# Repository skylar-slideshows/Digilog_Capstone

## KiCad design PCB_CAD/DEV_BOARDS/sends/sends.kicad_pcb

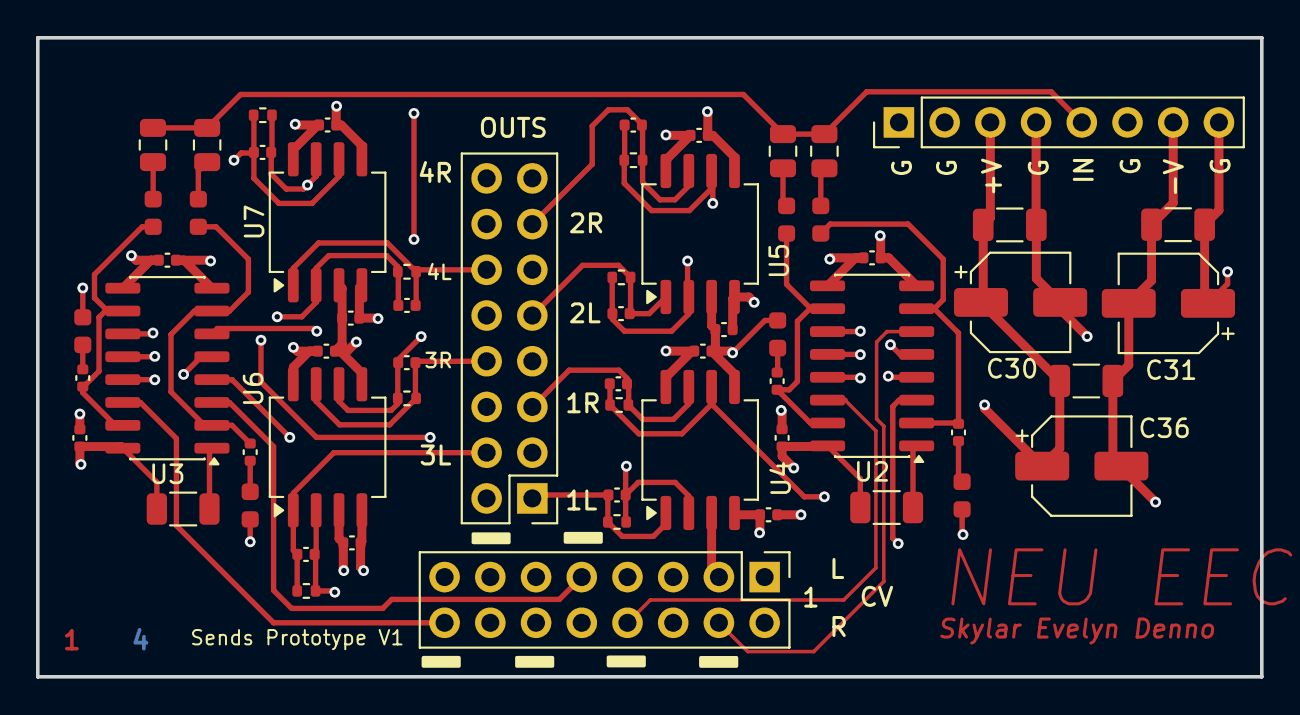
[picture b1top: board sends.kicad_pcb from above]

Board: 4 copper layers, 68.0 x 35.5 mm, 61 parts (0 on the bottom side), 42 nets.

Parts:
C1, C2, C3, C4, C5, C6, C7, C8: 100p; C_0402_1005Metric
C9, C11, C13, C14: 2.2u; C_0805_2012Metric
C10, C12, C15, C16: 1.2n; C_0402_1005Metric
C18, C19, C20, C21, C22, C23, C24, C25, C26, C27, C28, C29: 100n; C_0402_1005Metric
C30, C31, C36: 10u; CP_Elec_5x5.8
C34, C35, C37: 1u; C_1206_3216Metric
J1, J2: Conn_02x08_Odd_Even; PinHeader_2x08_P2.54mm_Vertical
J3: Conn_01x08_Pin; PinHeader_1x08_P2.54mm_Vertical
R1, R2, R3, R4, R5, R6, R7, R8: 20k; R_0402_1005Metric
R9, R11, R13, R14: 10k; R_0603_1608Metric
R10, R12, R15, R16: 220; R_0603_1608Metric
R17, R18: 15k; R_1206_3216Metric
U2, U3: SSI2164; SOIC-16_3.9x9.9mm_P1.27mm
U4, U5, U6, U7: NE5532; SOIC-8_5.3x6.2mm_P1.27mm

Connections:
1_1L: C1.2, J2.1, R1.2, U4.1
1_1R: C2.2, J2.5, R2.2, U4.7
1_2L: C3.2, J2.9, R3.2, U5.1
1_2R: C4.2, J2.13, R4.2, U5.7
1_3L: C5.2, J2.4, R5.2, U6.1
1_3R: C6.2, J2.8, R6.2, U6.7
1_4L: C7.2, J2.12, R7.2, U7.1
1_4R: C8.2, J2.16, R8.2, U7.7
1_IN: C9.1, C11.1, C13.1, C14.1, J3.5
1_send1L: J1.1, U2.3 (VC1)
1_send1R: J1.4, U2.6 (VC2)
1_send2L: J1.5, U2.11 (VC3)
1_send2R: J1.8, U2.14 (VC4)
1_send3L: J1.9, U3.3 (VC1)
1_send3R: J1.12, U3.6 (VC2)
1_send4L: J1.13, U3.11 (VC3)
1_send4R: J1.16, U3.14 (VC4)
+16.6V: C18.1, C20.1, C22.1, C24.1, C26.1, C28.1, C30.1, C34.1, C36.1, C37.1, J3.3, R17.1, R18.1, U2.16 (V+), U3.16 (V+), U4.8 (V+), U5.8 (V+), U6.8 (V+), U7.8 (V+)
-16.6V: C19.1, C21.1, C23.1, C25.1, C27.1, C29.1, C31.2, C35.1, C36.2, C37.2, J3.7, U2.9 (V-), U3.9 (V-), U4.4 (V-), U5.4 (V-), U6.4 (V-), U7.4 (V-)
GND: C18.2, C19.2, C20.2, C21.2, C22.2, C23.2, C24.2, C25.2, C26.2, C27.2, C28.2, C29.2, C30.2, C31.1, C34.2, C35.2, J1.2, J1.3, J1.6, J1.7, J1.10, J1.11, J1.14, J1.15, J2.2, J2.3, J2.6, J2.7, J2.10, J2.11, J2.14, J2.15, J3.1, J3.2, J3.4, J3.6, J3.8, R10.2, R12.2, R15.2, R16.2, U2.8 (GND), U3.8 (GND), U4.3 (+), U4.5 (+), U5.3 (+), U5.5 (+), U6.3 (+), U6.5 (+), U7.3 (+), U7.5 (+)
unnamed: C9.2, R9.1
unnamed: C10.2, R10.1
unnamed: C11.2, R11.1
unnamed: C12.2, R12.1
unnamed: C13.2, R13.1
unnamed: C14.2, R14.1
unnamed: C15.2, R15.1
unnamed: C16.2, R16.1
unnamed: C10.1, R9.2, U2.2 (I_IN1), U2.7 (I_IN2)
unnamed: C12.1, R11.2, U2.10 (I_IN3), U2.15 (I_IN4)
unnamed: C1.1, R1.1, U2.4 (I_OUT1), U4.2 (-)
unnamed: C2.1, R2.1, U2.5 (I_OUT2), U4.6 (-)
unnamed: C3.1, R3.1, U2.12 (I_OUT3), U5.2 (-)
unnamed: C4.1, R4.1, U2.13 (I_OUT4), U5.6 (-)
unnamed: R17.2, U2.1 (MODE)
unnamed: C15.1, R13.2, U3.2 (I_IN1), U3.7 (I_IN2)
unnamed: C16.1, R14.2, U3.10 (I_IN3), U3.15 (I_IN4)
unnamed: C5.1, R5.1, U3.4 (I_OUT1), U6.2 (-)
unnamed: C6.1, R6.1, U3.5 (I_OUT2), U6.6 (-)
unnamed: C7.1, R7.1, U3.12 (I_OUT3), U7.2 (-)
unnamed: C8.1, R8.1, U3.13 (I_OUT4), U7.6 (-)
unnamed: R18.2, U3.1 (MODE)

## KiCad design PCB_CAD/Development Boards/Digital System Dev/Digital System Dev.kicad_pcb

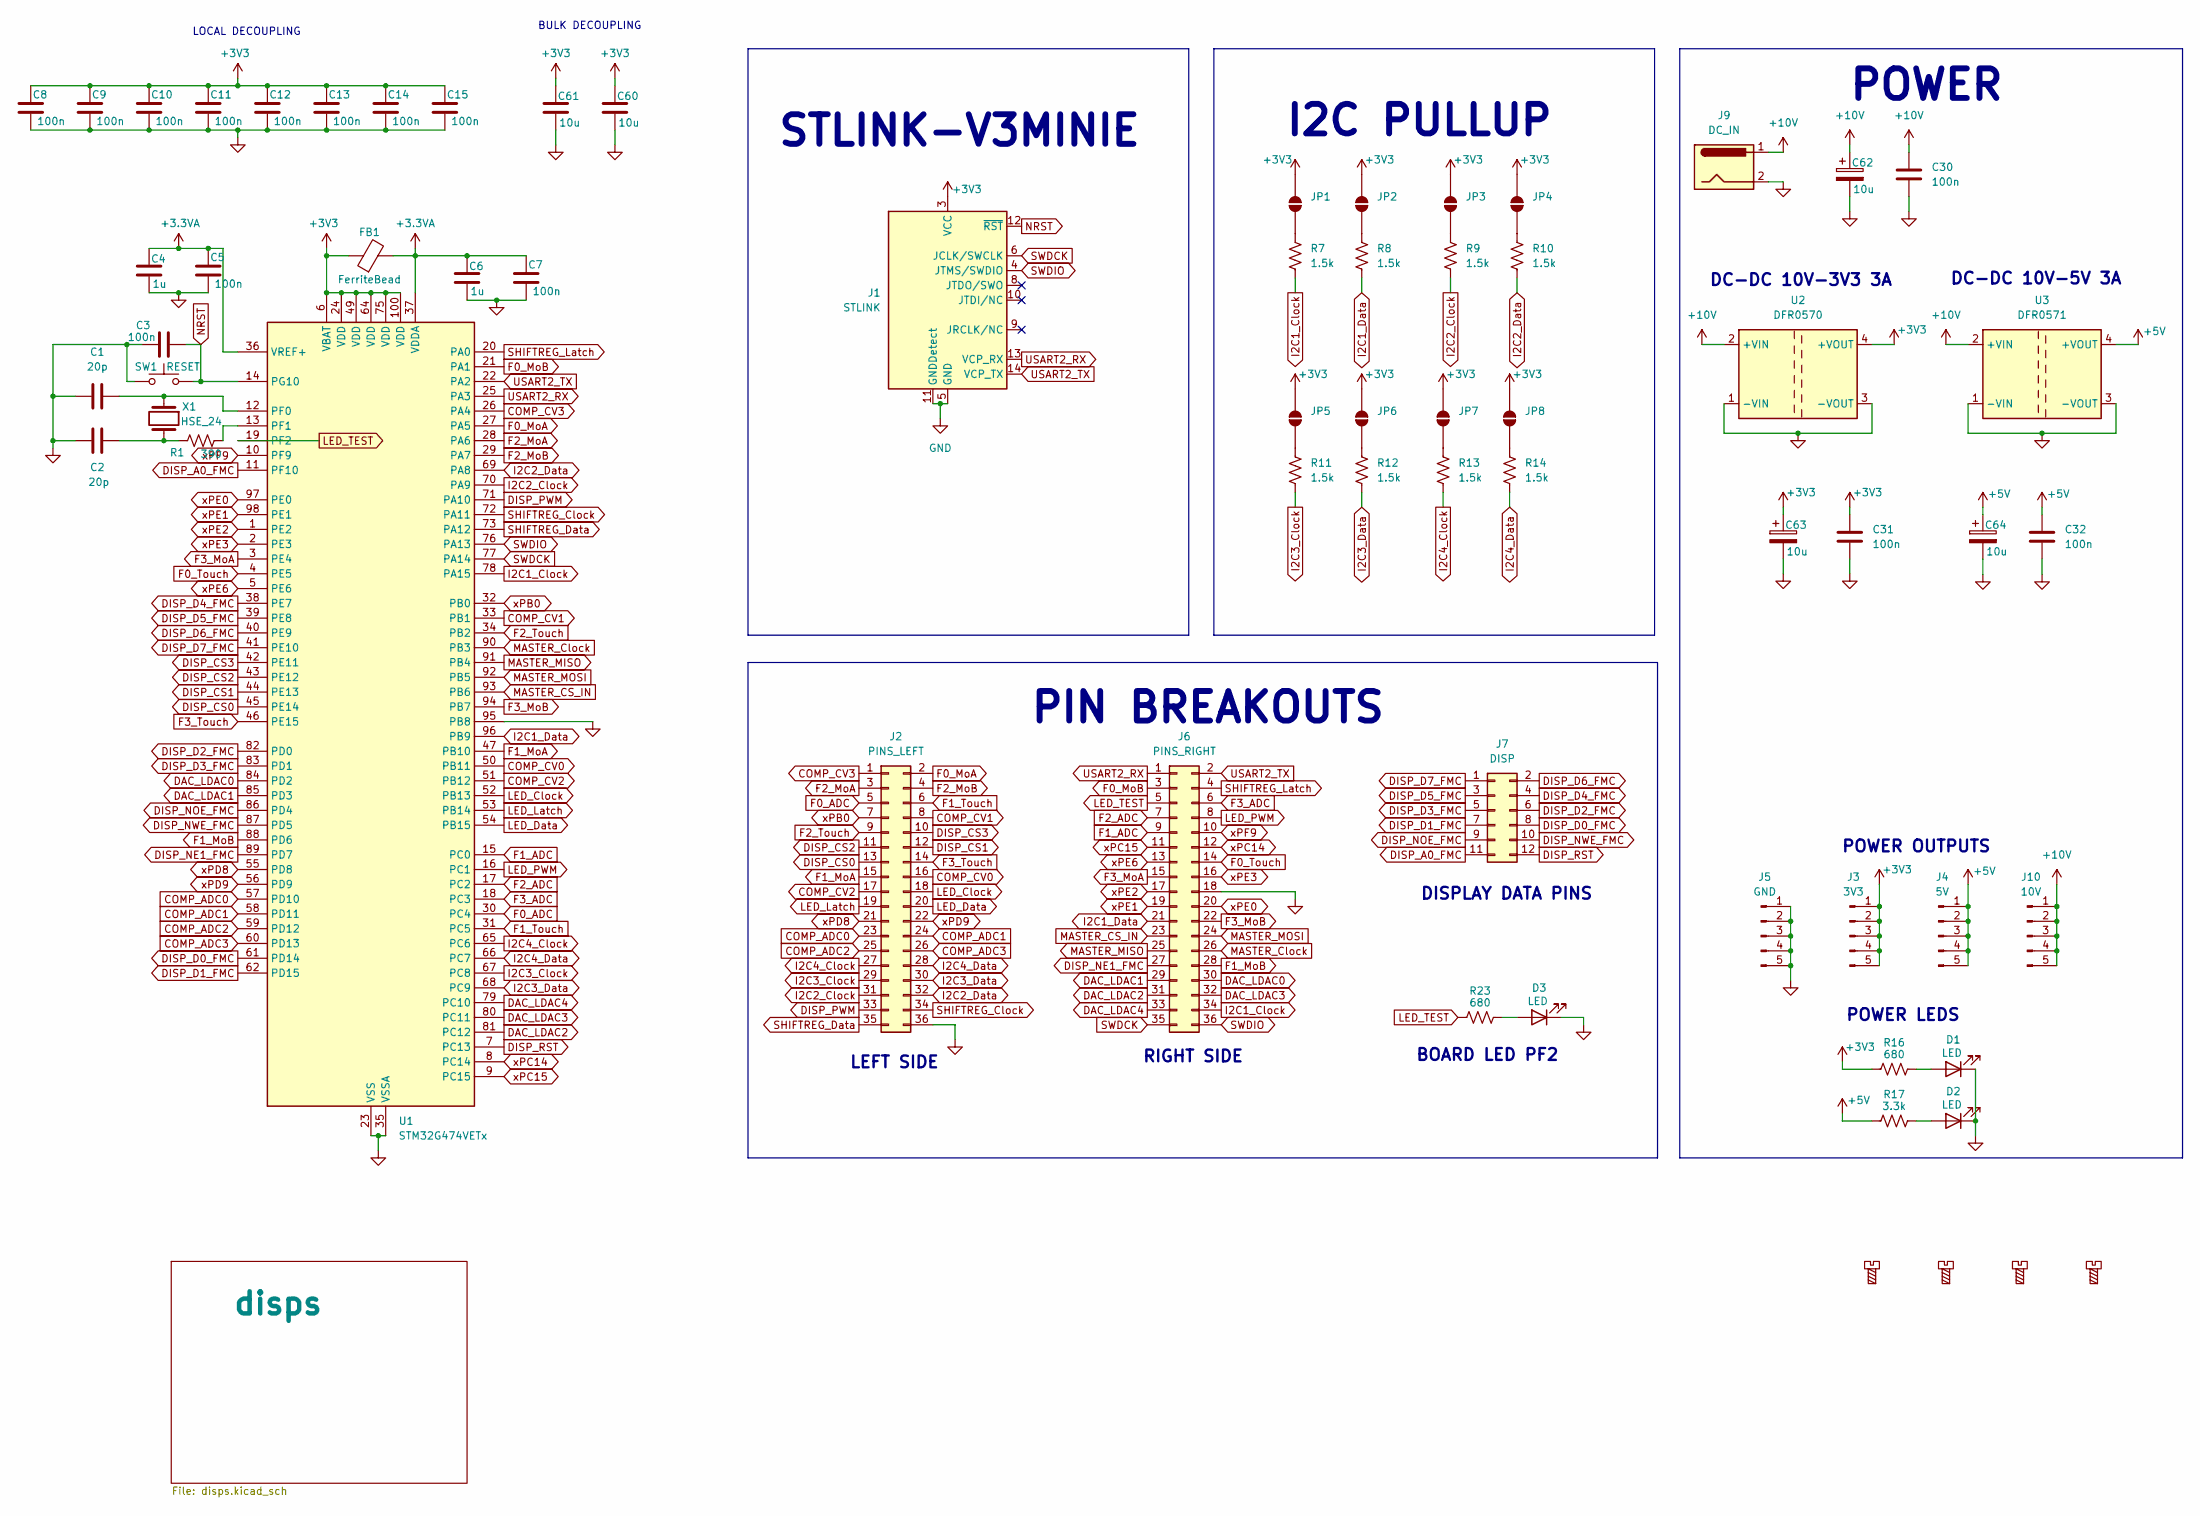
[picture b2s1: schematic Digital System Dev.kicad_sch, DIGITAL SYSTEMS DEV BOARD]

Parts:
C1, C2: 20p; C_0603_1608Metric; LCSC C1648
C3, C5, C7, C8, C9, C10, C11, C12, C13, C14, C15, C30, C31, C32: 100n; C_0603_1608Metric; LCSC C1590
C4, C6: 1u; C_0603_1608Metric; LCSC C1592
C60, C61: 10u; C_1206_3216Metric; LCSC C1849
C62, C63, C64: 10u; CP_Elec_6.3x5.8; LCSC C48970664
D1, D2, D3: LED; LED_0603_1608Metric; LCSC C12065
FB1: FerriteBead; Ferrite_0603_1608Metric; LCSC C1002
H1, H2, H3, H4: MountingScrew; MountingHole_3.2mm_M3; LCSC DNP
J1: STLINK; FTSH-107-01-L-DV-K-TR; LCSC C5307809
J2: PINS_LEFT; PinHeader_2x18_P2.54mm_Vertical; LCSC DNP
J3: 3V3; PinSocket_1x05_P2.54mm_Vertical; LCSC DNP
J4: 5V; PinSocket_1x05_P2.54mm_Vertical; LCSC DNP
J5: GND; PinSocket_1x05_P2.54mm_Vertical; LCSC DNP
J6: PINS_RIGHT; PinHeader_2x18_P2.54mm_Vertical; LCSC DNP
J7: DISP; PinHeader_2x06_P2.54mm_Vertical; LCSC DNP
J9: DC_IN; BarrelJack_Horizontal; LCSC DNP
J10: 10V; PinSocket_1x05_P2.54mm_Vertical; LCSC DNP
JP1, JP2, JP3, JP4, JP5, JP6, JP7, JP8: SolderJumper_2_Open; SolderJumper-2_P1.3mm_Open_TrianglePad1.0x1.5mm; LCSC DNP
R1: 390; R_1206_3216Metric; LCSC C4491
R7, R8, R9, R10, R11, R12, R13, R14: 1.5k; R_0603_1608Metric; LCSC C22843
R16, R23: 680; R_0603_1608Metric; LCSC C23228
R17: 3.3k; R_0603_1608Metric; LCSC C22978
SW1: RESET; SW_Push_1P1T_NO_CK_KMR2; LCSC C72443
U1: STM32G474VETx; LQFP-100_14x14mm_P0.5mm; LCSC C2970837
U2: DFR0570; DFR05xx_DC-DC; LCSC DNP
U3: DFR0571; DFR05xx_DC-DC; LCSC DNP
X1: HSE_24; Crystal_SMD_HC49-SD; LCSC C2253

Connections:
+3.3VA: C4.1, C5.1, C6.1, C7.1, FB1.2, U1.36 (VREF+), U1.37 (VDDA)
+3V3: C8.1, C9.1, C10.1, C11.1, C12.1, C13.1, C14.1, C15.1, C31.1, C60.1, C61.1, C63.1, FB1.1, J1.3 (VCC), J3.1, J3.2, J3.3, J3.4, J3.5, JP1.2 (B), JP2.2 (B), JP3.2 (B), JP4.2 (B), JP5.2 (B), JP6.2 (B), JP7.2 (B), JP8.2 (B), R16.1, U1.6 (VBAT), U1.24 (VDD), U1.49 (VDD), U1.64 (VDD), U1.75 (VDD), U1.100 (VDD), U2.4 (+VOUT); also elsewhere on the board
+5V: C32.1, C64.1, J4.1, J4.2, J4.3, J4.4, J4.5, R17.1, U3.4 (+VOUT); also elsewhere on the board
+10V: C30.1, C62.1, J9.1, J10.1, J10.2, J10.3, J10.4, J10.5, U2.2 (+VIN), U3.2 (+VIN)
COMP_ADC0: J2.23, U1.57 (PD10)
COMP_ADC1: J2.24, U1.58 (PD11)
COMP_ADC2: J2.25, U1.59 (PD12)
COMP_ADC3: J2.26, U1.60 (PD13)
COMP_CV0: J2.16, U1.50 (PB11)
COMP_CV1: J2.8, U1.33 (PB1)
COMP_CV2: J2.17, U1.51 (PB12)
COMP_CV3: J2.1, U1.26 (PA4)
DAC_LDAC0: J6.30, U1.84 (PD2)
DAC_LDAC1: J6.29, U1.85 (PD3)
DAC_LDAC2: J6.31, U1.81 (PC12)
DAC_LDAC3: J6.32, U1.80 (PC11)
DAC_LDAC4: J6.33, U1.79 (PC10)
DISP_A0_FMC: J7.11, U1.11 (PF10); also elsewhere on the board
DISP_CS0: J2.13, U1.45 (PE14); also elsewhere on the board
DISP_CS1: J2.12, U1.44 (PE13); also elsewhere on the board
DISP_CS2: J2.11, U1.43 (PE12); also elsewhere on the board
DISP_CS3: J2.10, U1.42 (PE11); also elsewhere on the board
DISP_D0_FMC: J7.8, U1.61 (PD14); also elsewhere on the board
DISP_D1_FMC: J7.7, U1.62 (PD15); also elsewhere on the board
DISP_D2_FMC: J7.6, U1.82 (PD0); also elsewhere on the board
DISP_D3_FMC: J7.5, U1.83 (PD1); also elsewhere on the board
DISP_D4_FMC: J7.4, U1.38 (PE7); also elsewhere on the board
DISP_D5_FMC: J7.3, U1.39 (PE8); also elsewhere on the board
DISP_D6_FMC: J7.2, U1.40 (PE9); also elsewhere on the board
DISP_D7_FMC: J7.1, U1.41 (PE10); also elsewhere on the board
DISP_NE1_FMC: J6.27, U1.89 (PD7)
DISP_NOE_FMC: J7.9, U1.86 (PD4); also elsewhere on the board
DISP_NWE_FMC: J7.10, U1.87 (PD5); also elsewhere on the board
DISP_PWM: J2.33, U1.71 (PA10); also elsewhere on the board
DISP_RST: J7.12, U1.7 (PC13); also elsewhere on the board
F0_ADC: J2.5, U1.30 (PC4)
F0_MoA: J2.2, U1.27 (PA5)
F0_MoB: J6.3, U1.21 (PA1)
F0_Touch: J6.14, U1.4 (PE5)
F1_ADC: J6.9, U1.15 (PC0)
F1_MoA: J2.15, U1.47 (PB10)
F1_MoB: J6.28, U1.88 (PD6)
F1_Touch: J2.6, U1.31 (PC5)
F2_ADC: J6.7, U1.17 (PC2)
F2_MoA: J2.3, U1.28 (PA6)
F2_MoB: J2.4, U1.29 (PA7)
F2_Touch: J2.9, U1.34 (PB2)
F3_ADC: J6.6, U1.18 (PC3)
F3_MoA: J6.15, U1.3 (PE4)
F3_MoB: J6.22, U1.94 (PB7)
F3_Touch: J2.14, U1.46 (PE15)
GND: C1.2, C2.1, C3.1, C4.2, C5.2, C6.2, C7.2, C8.2, C9.2, C10.2, C11.2, C12.2, C13.2, C14.2, C15.2, C30.2, C31.2, C32.2, C60.2, C61.2, C62.2, C63.2, C64.2, D1.1 (K), D2.1 (K), D3.1 (K), J1.5 (GND), J1.7 (GND), J1.11 (GNDDetect), J2.36, J2.MP (MountPin), J5.1, J5.2, J5.3, J5.4, J5.5, J6.18, J6.MP (MountPin), J9.2, SW1.1, U1.23 (VSS), U1.35 (VSSA), U1.48 (VSS), U1.63 (VSS), U1.74 (VSS), U1.95 (PB8), U1.99 (VSS), U2.1 (-VIN), U2.3 (-VOUT), U3.1 (-VIN), U3.3 (-VOUT); also elsewhere on the board
I2C1_Clock: J6.34, R7.2, U1.78 (PA15)
I2C1_Data: J6.21, R8.2, U1.96 (PB9)
I2C2_Clock: J2.31, R9.2, U1.70 (PA9)
I2C2_Data: J2.32, R10.2, U1.69 (PA8)
I2C3_Clock: J2.29, R11.2, U1.67 (PC8)
I2C3_Data: J2.30, R12.2, U1.68 (PC9)
I2C4_Clock: J2.27, R13.2, U1.65 (PC6)
I2C4_Data: J2.28, R14.2, U1.66 (PC7)
LED_Clock: J2.18, U1.52 (PB13)
LED_Data: J2.20, U1.54 (PB15)
LED_Latch: J2.19, U1.53 (PB14)
LED_PWM: J6.8, U1.16 (PC1)
LED_TEST: J6.5, R23.1, U1.19 (PF2)
MASTER_CS_IN: J6.23, U1.93 (PB6)
MASTER_Clock: J6.26, U1.90 (PB3)
MASTER_MISO: J6.25, U1.91 (PB4)
MASTER_MOSI: J6.24, U1.92 (PB5)
NRST: C3.2, J1.12 (~RST), SW1.2, U1.14 (PG10)
unnamed: C2.2, R1.1, X1.2
unnamed: D1.2 (A), R16.2
unnamed: D2.2 (A), R17.2
unnamed: D3.2 (A), R23.2
unnamed: JP1.1 (A), R7.1
unnamed: JP2.1 (A), R8.1
unnamed: JP3.1 (A), R9.1
unnamed: JP4.1 (A), R10.1
unnamed: JP5.1 (A), R11.1
unnamed: JP6.1 (A), R12.1
unnamed: JP7.1 (A), R13.1
unnamed: JP8.1 (A), R14.1
unnamed: C1.1, U1.12 (PF0), X1.1
unnamed: R1.2, U1.13 (PF1)
SHIFTREG_Clock: J2.34, U1.72 (PA11)
SHIFTREG_Data: J2.35, U1.73 (PA12)
SHIFTREG_Latch: J6.4, U1.20 (PA0)
SWDCK: J1.6 (JCLK/SWCLK), J6.35, U1.77 (PA14)
SWDIO: J1.4 (JTMS/SWDIO), J6.36, U1.76 (PA13)
USART2_RX: J1.13 (VCP_RX), J6.1, U1.25 (PA3)
USART2_TX: J1.14 (VCP_TX), J6.2, U1.22 (PA2)
xPB0: J2.7, U1.32 (PB0)
xPC14: J6.12, U1.8 (PC14)
xPC15: J6.11, U1.9 (PC15)
xPD8: J2.21, U1.55 (PD8)
xPD9: J2.22, U1.56 (PD9)
xPE0: J6.20, U1.97 (PE0)
xPE1: J6.19, U1.98 (PE1)
xPE2: J6.17, U1.1 (PE2)
xPE3: J6.16, U1.2 (PE3)
xPE6: J6.13, U1.5 (PE6)
xPF9: J6.10, U1.10 (PF9)

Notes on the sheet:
I2C PULLUP
BULK DECOUPLING
POWER LEDS
STLINK-V3MINIE
POWER OUTPUTS
DISPLAY DATA PINS
POWER
PIN BREAKOUTS
LOCAL DECOUPLING
DC-DC 10V-5V 3A
DC-DC 10V-3V3 3A
BOARD LED PF2
LEFT SIDE
RIGHT SIDE

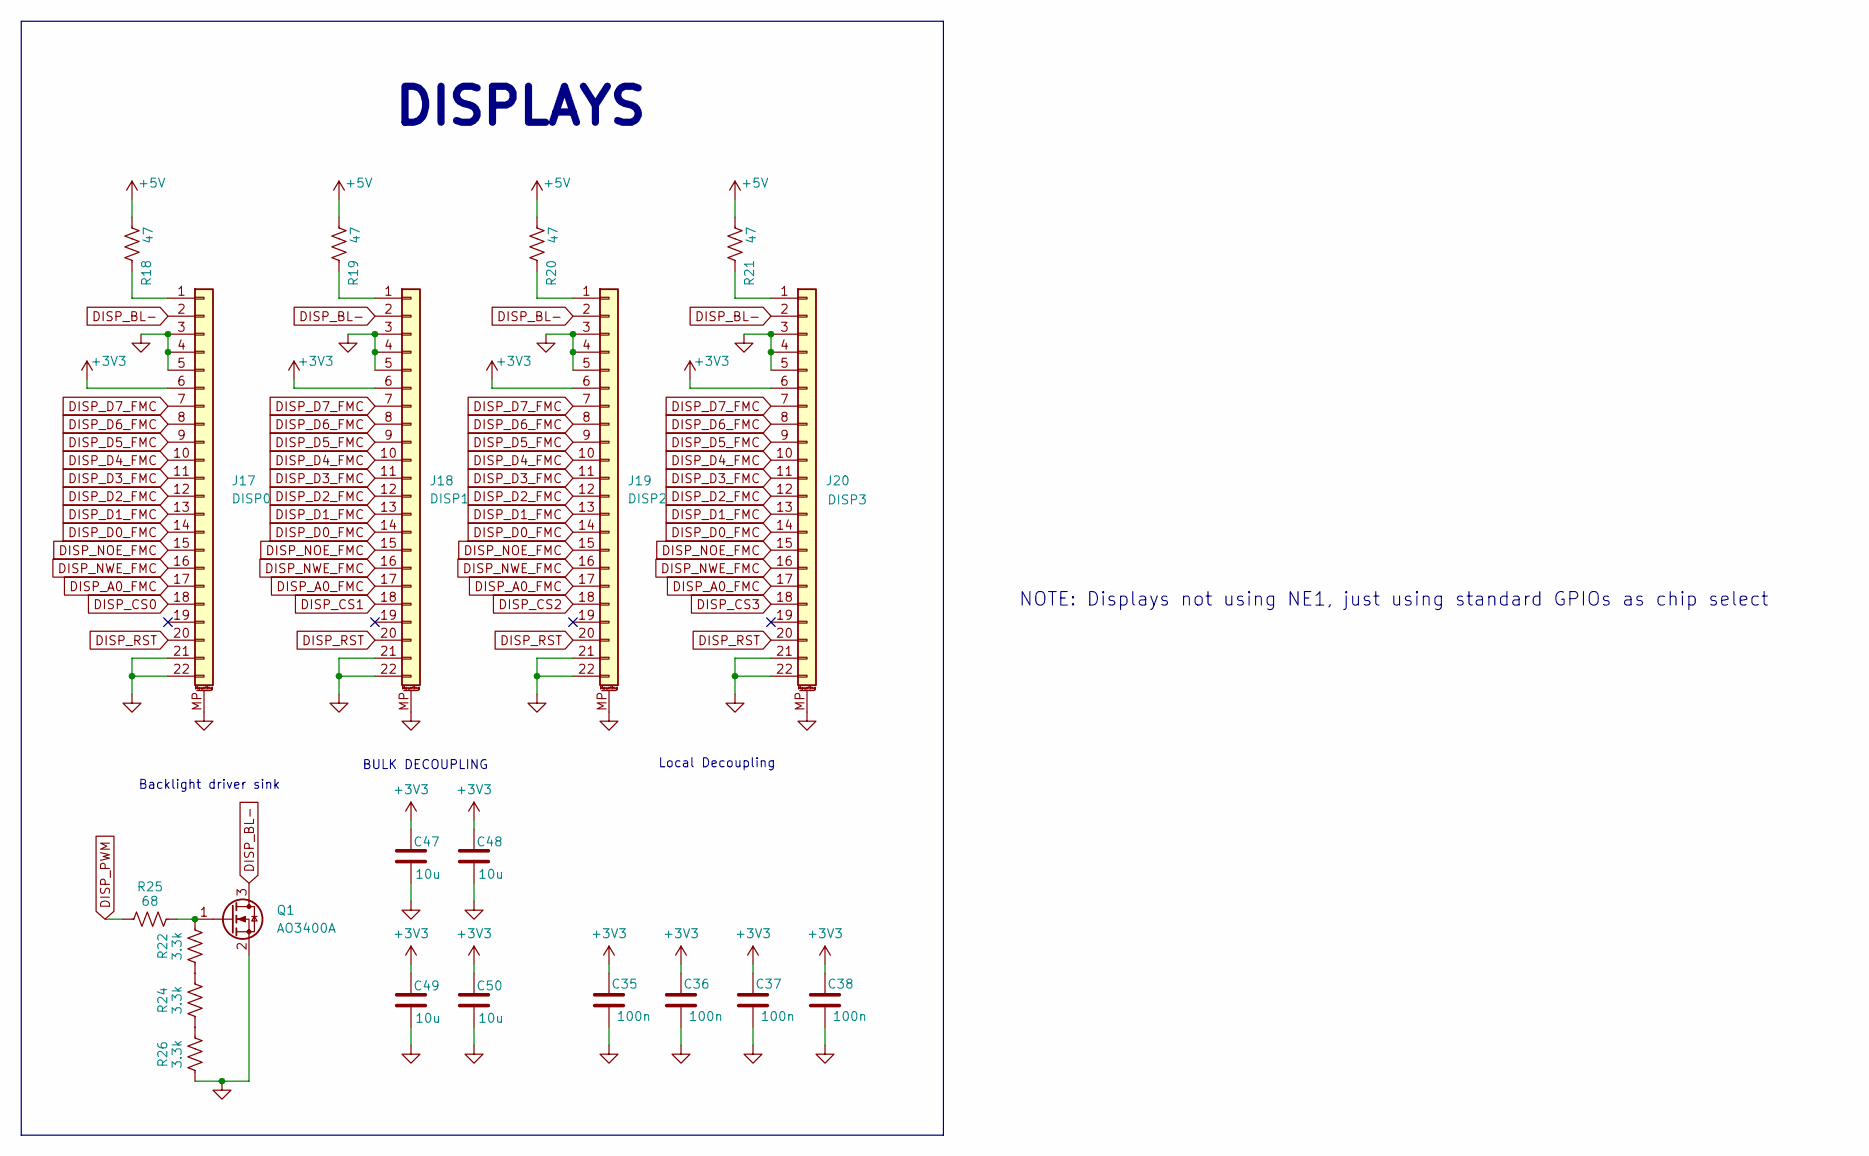
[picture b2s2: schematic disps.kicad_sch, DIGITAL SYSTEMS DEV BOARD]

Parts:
C35, C36, C37, C38: 100n; C_0603_1608Metric; LCSC C1590
C47, C48, C49, C50: 10u; C_1206_3216Metric; LCSC C1849
J17: DISP0; TE_2-1734839-2_1x22-1MP_P0.5mm_Horizontal; LCSC C22435644
J18: DISP1; TE_2-1734839-2_1x22-1MP_P0.5mm_Horizontal; LCSC C22435644
J19: DISP2; TE_2-1734839-2_1x22-1MP_P0.5mm_Horizontal; LCSC C22435644
J20: DISP3; TE_2-1734839-2_1x22-1MP_P0.5mm_Horizontal; LCSC C22435644
Q1: AO3400A; SOT-23; LCSC C20917
R18, R19, R20, R21: 47; R_1206_3216Metric; LCSC C17969
R22, R24, R26: 3.3k; R_0603_1608Metric; LCSC C22978
R25: 68; R_1206_3216Metric; LCSC C294793

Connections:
+3V3: C35.1, C36.1, C37.1, C38.1, C47.1, C48.1, C49.1, C50.1, J17.6, J18.6, J19.6, J20.6; also elsewhere on the board
+5V: R18.2, R19.2, R20.2, R21.2; also elsewhere on the board
DISP_A0_FMC: J17.17, J18.17, J19.17, J20.17; also elsewhere on the board
DISP_BL-: J17.2, J18.2, J19.2, J20.2, Q1.3 (D)
DISP_CS0: J17.18; also elsewhere on the board
DISP_CS1: J18.18; also elsewhere on the board
DISP_CS2: J19.18; also elsewhere on the board
DISP_CS3: J20.18; also elsewhere on the board
DISP_D0_FMC: J17.14, J18.14, J19.14, J20.14; also elsewhere on the board
DISP_D1_FMC: J17.13, J18.13, J19.13, J20.13; also elsewhere on the board
DISP_D2_FMC: J17.12, J18.12, J19.12, J20.12; also elsewhere on the board
DISP_D3_FMC: J17.11, J18.11, J19.11, J20.11; also elsewhere on the board
DISP_D4_FMC: J17.10, J18.10, J19.10, J20.10; also elsewhere on the board
DISP_D5_FMC: J17.9, J18.9, J19.9, J20.9; also elsewhere on the board
DISP_D6_FMC: J17.8, J18.8, J19.8, J20.8; also elsewhere on the board
DISP_D7_FMC: J17.7, J18.7, J19.7, J20.7; also elsewhere on the board
DISP_NOE_FMC: J17.15, J18.15, J19.15, J20.15; also elsewhere on the board
DISP_NWE_FMC: J17.16, J18.16, J19.16, J20.16; also elsewhere on the board
DISP_PWM: R25.1; also elsewhere on the board
DISP_RST: J17.20, J18.20, J19.20, J20.20; also elsewhere on the board
GND: C35.2, C36.2, C37.2, C38.2, C47.2, C48.2, C49.2, C50.2, J17.3, J17.4, J17.5, J17.21, J17.22, J17.MP (MountPin), J18.3, J18.4, J18.5, J18.21, J18.22, J18.MP (MountPin), J19.3, J19.4, J19.5, J19.21, J19.22, J19.MP (MountPin), J20.3, J20.4, J20.5, J20.21, J20.22, J20.MP (MountPin), Q1.2 (S), R26.1; also elsewhere on the board
unnamed: J17.1, R18.1
unnamed: J18.1, R19.1
unnamed: J19.1, R20.1
unnamed: J20.1, R21.1
unnamed: Q1.1 (G), R22.2, R25.2
unnamed: R22.1, R24.2
unnamed: R24.1, R26.2

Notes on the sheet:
DISPLAYS
Local Decoupling
Backlight driver sink
NOTE: Displays not using NE1, just using standard GPIOs as chip select
BULK DECOUPLING

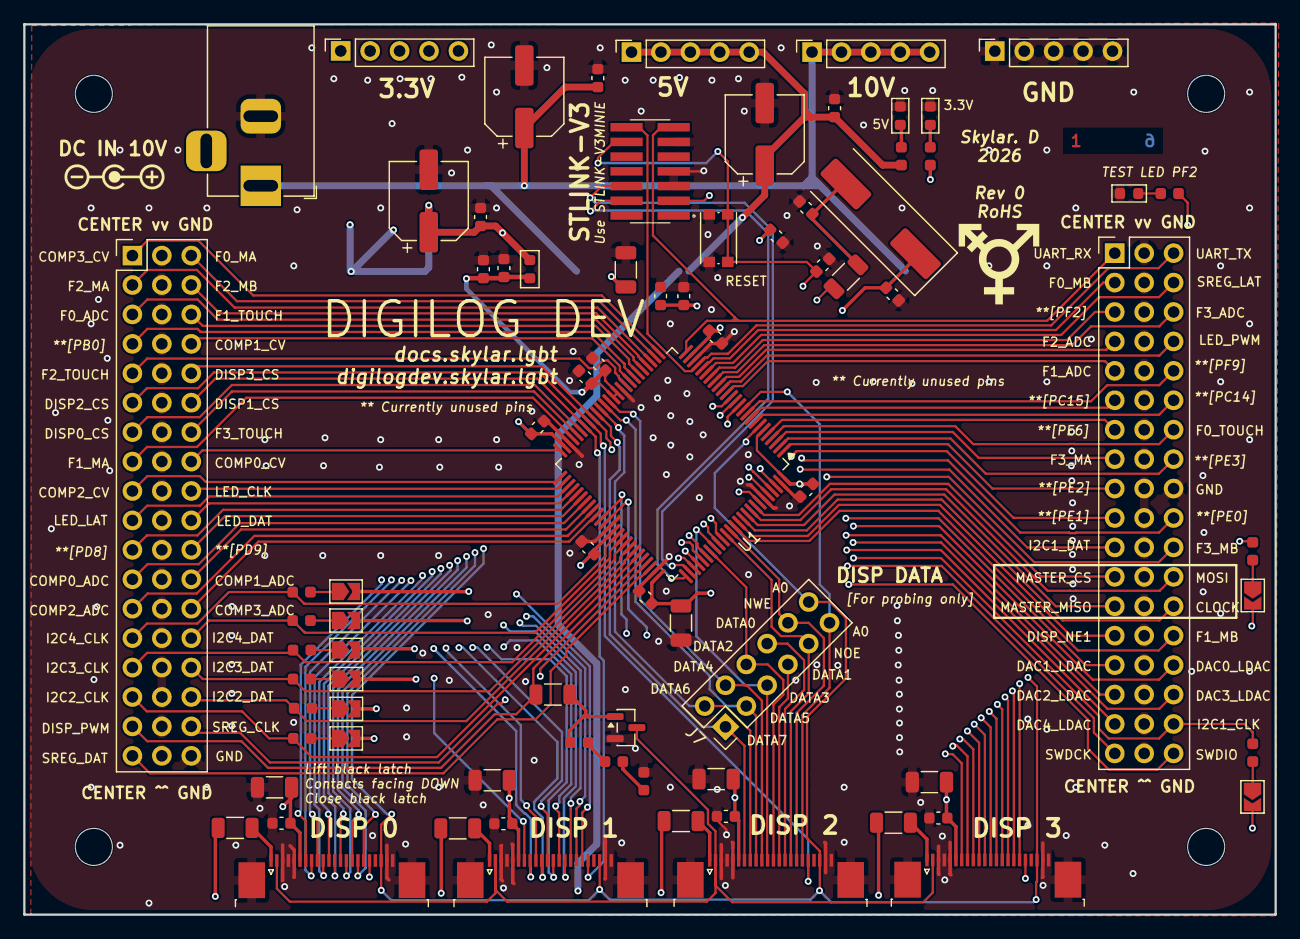
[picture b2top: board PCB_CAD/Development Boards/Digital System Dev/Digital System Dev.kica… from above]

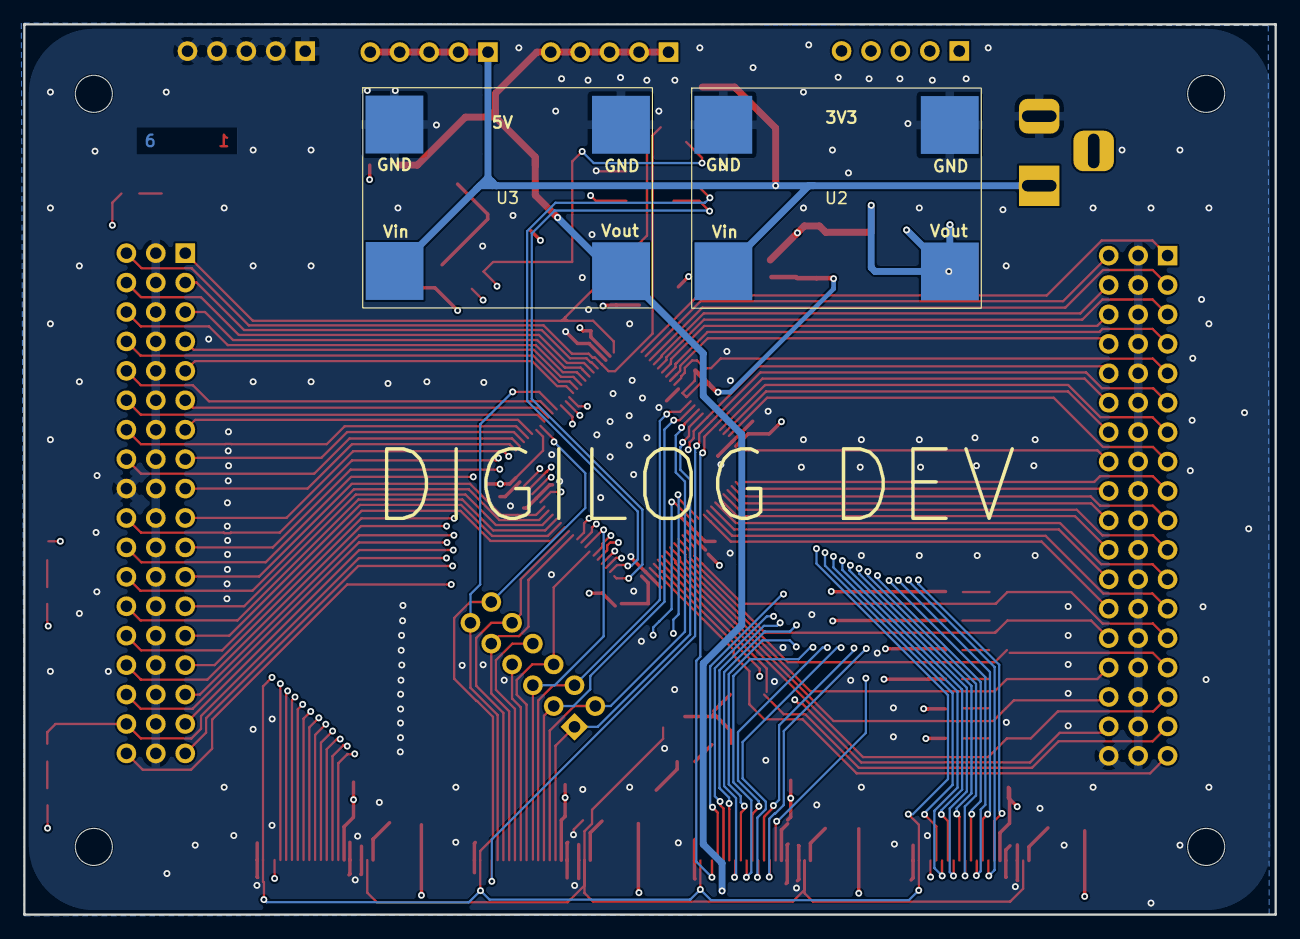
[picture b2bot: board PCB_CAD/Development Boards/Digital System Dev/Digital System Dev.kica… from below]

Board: 6 copper layers, 108.0 x 76.8 mm, 86 parts (2 on the bottom side), 110 nets.

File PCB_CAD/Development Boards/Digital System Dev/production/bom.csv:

Designator,Footprint,Quantity,Value,LCSC Part #
"C1, C2",0603,2,20p,C1648
"C10, C11, C12, C13, C14, C15, C3, C30, C31, C32, C35, C36, C37, C38, C5, C7, C8, C9",0603,18,100n,C1590
"C4, C6",0603,2,1u,C1592
"C47, C48, C49, C50, C60, C61",1206,6,10u,C1849
"C62, C63, C64",CP_Elec_6.3x5.8,3,10u,C48970664
"D1, D2, D3",0603,3,LED,C12065
FB1,Ferrite_0603_1608Metric,1,FerriteBead,C1002
J1,FTSH-107-01-L-DV-K-TR,1,STLINK,C5307809
J10,PinSocket_1x05_P2.54mm_Vertical,1,10V,DNP
J17,TE_2-1734839-2_1x22-1MP_P0.5mm_Horizontal,1,DISP0,C22435644
J18,TE_2-1734839-2_1x22-1MP_P0.5mm_Horizontal,1,DISP1,C22435644
J19,TE_2-1734839-2_1x22-1MP_P0.5mm_Horizontal,1,DISP2,C22435644
J2,PinHeader_2x18_P2.54mm_Vertical,1,PINS_LEFT,DNP
J20,TE_2-1734839-2_1x22-1MP_P0.5mm_Horizontal,1,DISP3,C22435644
J3,PinSocket_1x05_P2.54mm_Vertical,1,3V3,DNP
J4,PinSocket_1x05_P2.54mm_Vertical,1,5V,DNP
J5,PinSocket_1x05_P2.54mm_Vertical,1,GND,DNP
J6,PinHeader_2x18_P2.54mm_Vertical,1,PINS_RIGHT,DNP
J7,PinHeader_2x06_P2.54mm_Vertical,1,DISP,DNP
J9,BarrelJack_Horizontal,1,DC_IN,DNP
Q1,SOT-23,1,AO3400A,C20917
R1,1206,1,390,C4491
"R10, R11, R12, R13, R14, R7, R8, R9",0603,8,1.5k,C22843
"R16, R23",0603,2,680,C23228
"R17, R22, R24, R26",0603,4,3.3k,C22978
"R18, R19, R20, R21",1206,4,47,C17969
R25,1206,1,68,C294793
SW1,SW_Push_1P1T_NO_CK_KMR2,1,RESET,C72443
U1,LQFP-100_14x14mm_P0.5mm,1,STM32G474VETx,C2970837
U2,DFR05xx_DC-DC,1,DFR0570,DNP
U3,DFR05xx_DC-DC,1,DFR0571,DNP
X1,Crystal_SMD_HC49-SD,1,HSE_24,C2253
